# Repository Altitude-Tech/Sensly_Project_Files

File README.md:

# Sensly_Project_Files-
All files required for the production of the Sensly Air Quality Development Board

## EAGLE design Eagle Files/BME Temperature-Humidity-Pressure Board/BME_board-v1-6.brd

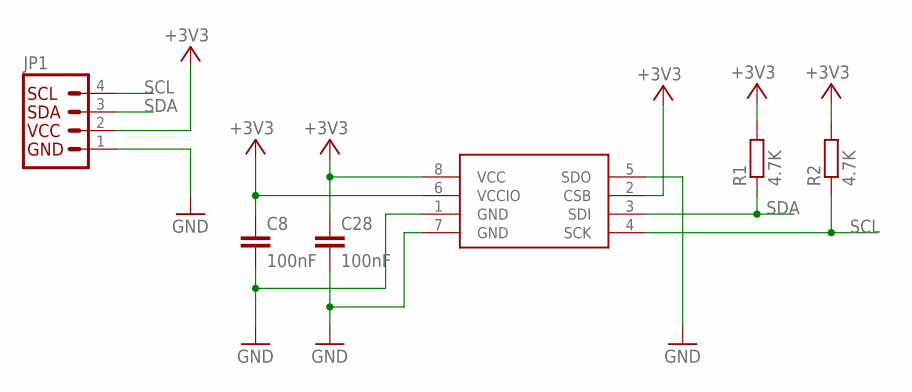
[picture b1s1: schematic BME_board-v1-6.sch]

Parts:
C8, C28: 100nF; C0603
IC2: BME280
JP1: I2C_STANDARD; 1X04
R1, R2: 4.7K; R0603

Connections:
+3V3: C8.1, C28.1, IC2.2 (CSB), IC2.6 (VCCIO), IC2.8 (VCC), JP1.2, R1.2, R2.2
GND: C8.2, C28.2, IC2.1 (GND), IC2.5 (SDO), IC2.7 (GND), JP1.1
SCL: IC2.4 (SCK), JP1.4, R2.1
SDA: IC2.3 (SDI), JP1.3, R1.1

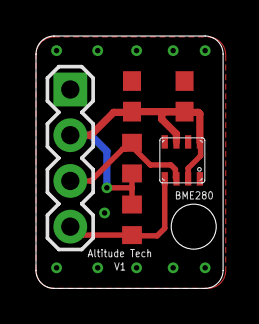
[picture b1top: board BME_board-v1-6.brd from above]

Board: 2 copper layers, 10.4 x 14.0 mm, 6 parts (0 on the bottom side), 4 nets.

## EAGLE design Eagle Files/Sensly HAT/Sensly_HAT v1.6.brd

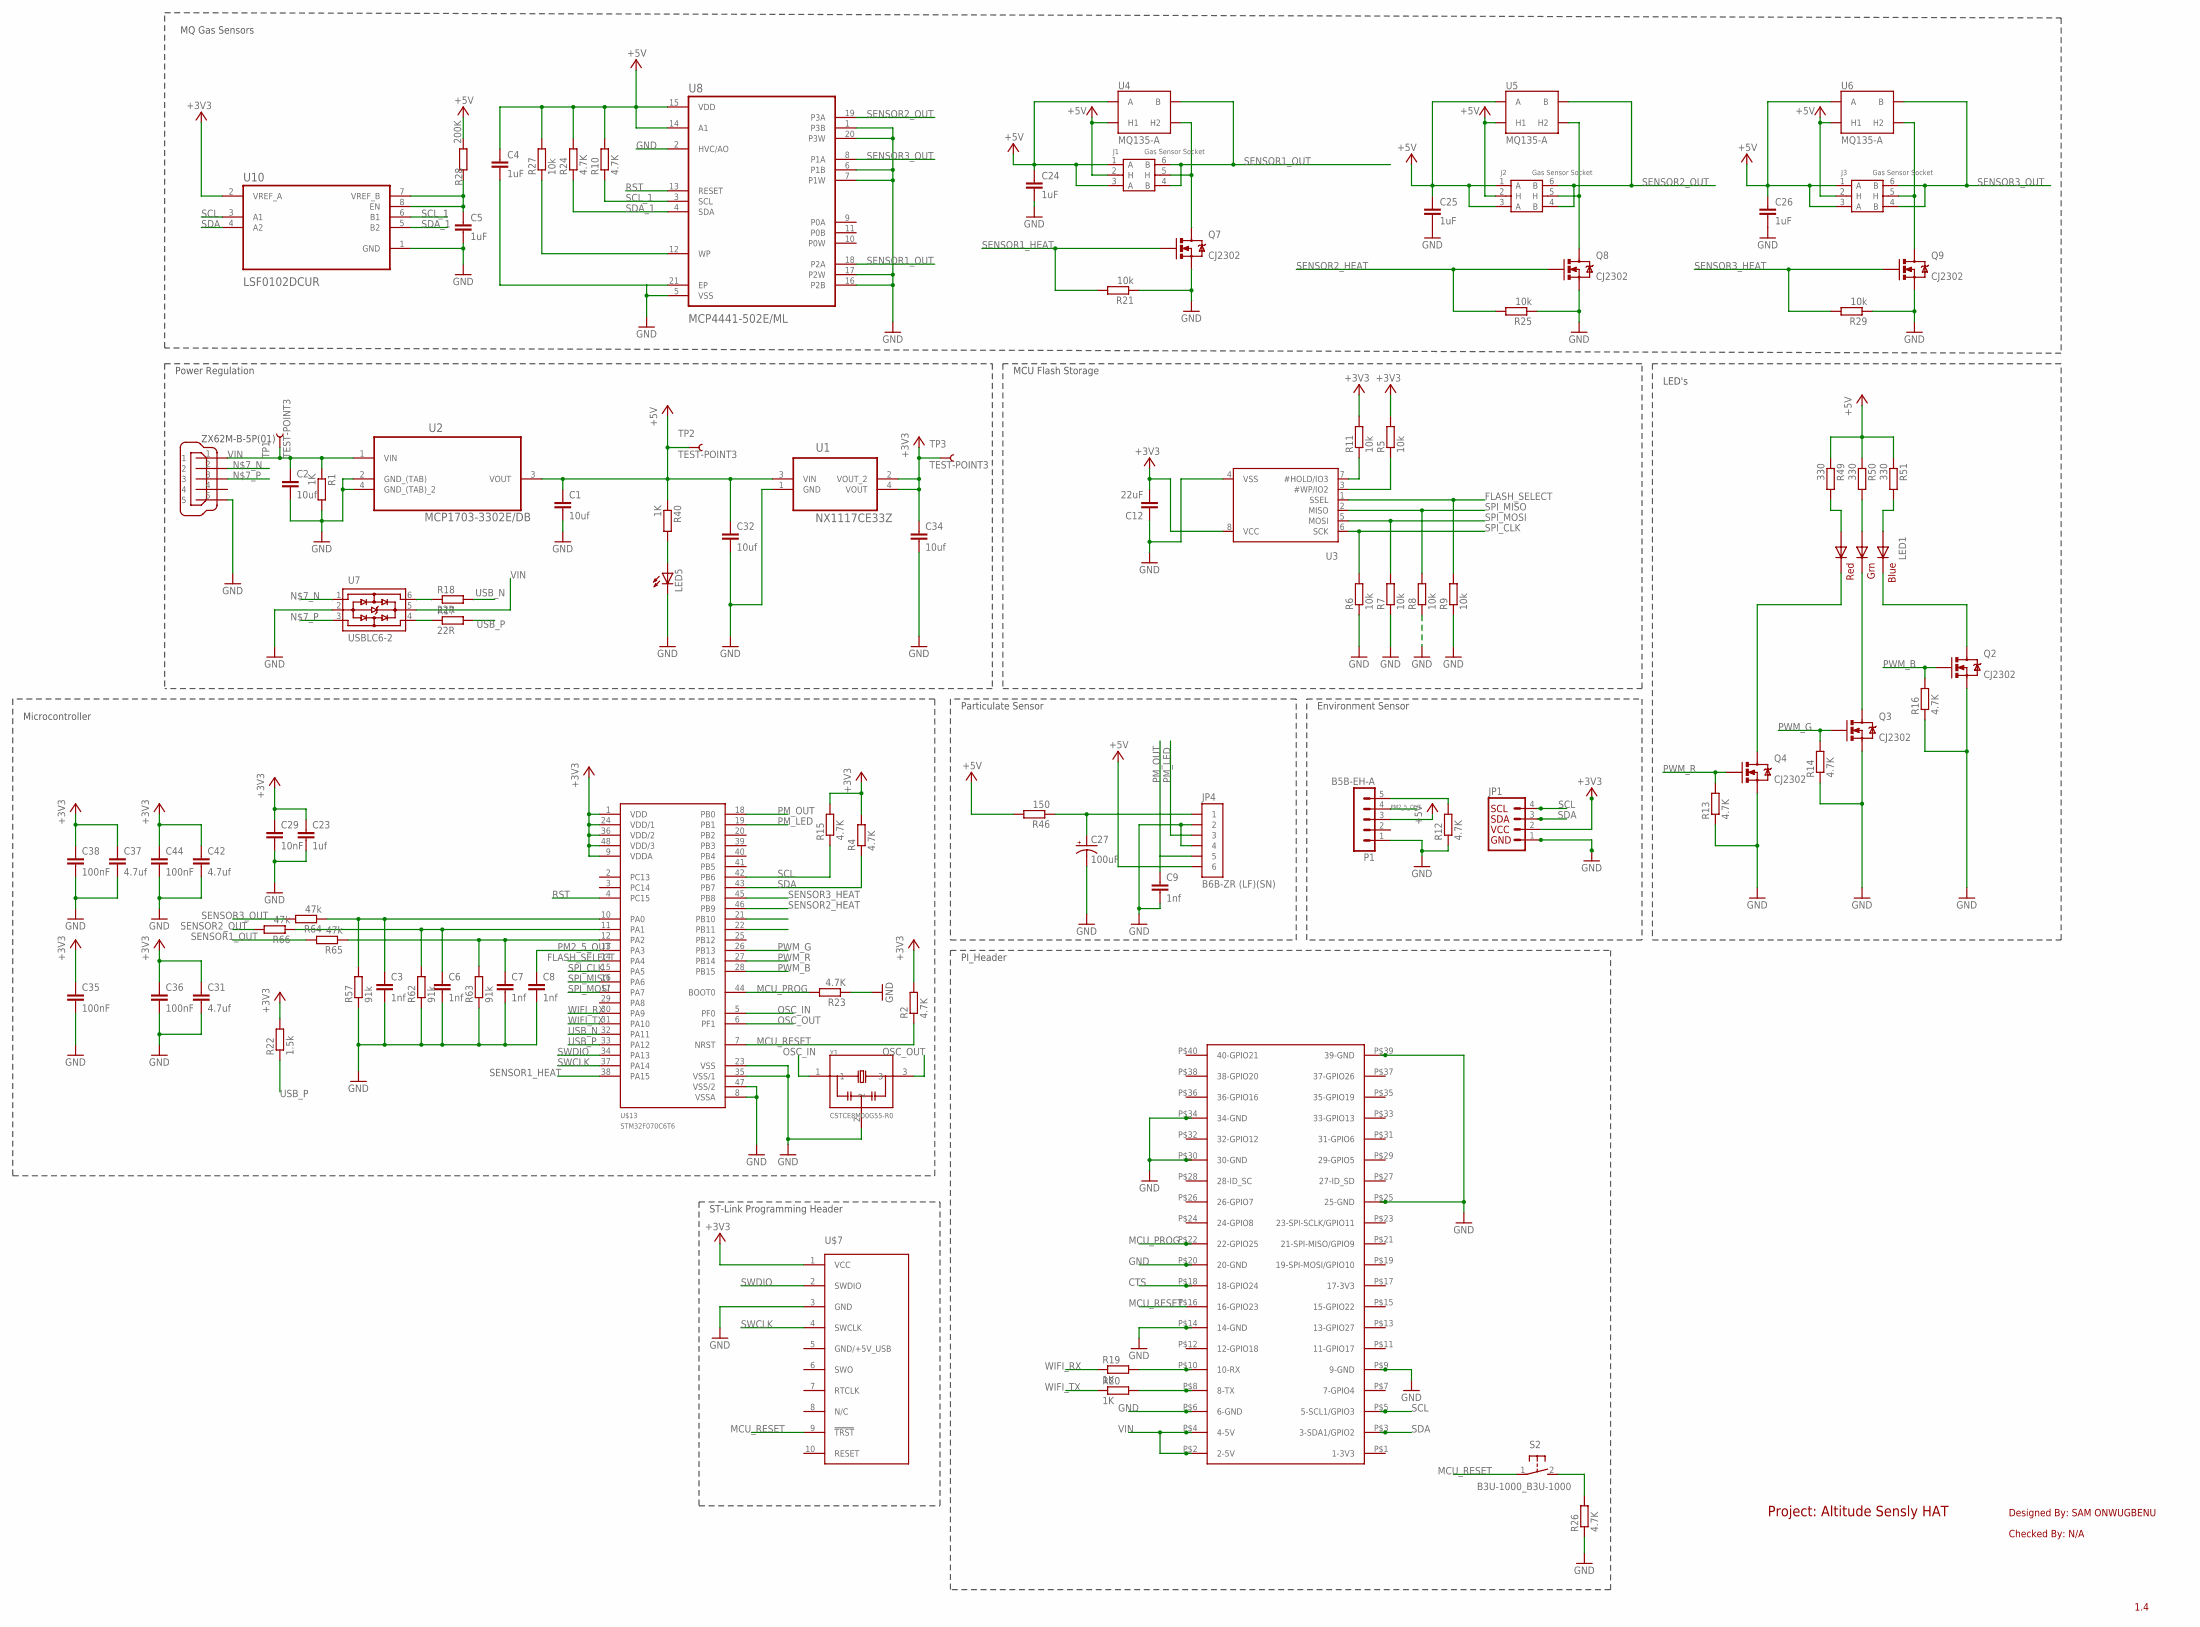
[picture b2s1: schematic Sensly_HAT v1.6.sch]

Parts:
C1, C2, C32, C34: 10uf; C0603
C3, C6, C7, C8, C9: 1nf; EAGLE-LTSPICE_C0402
C4, C5, C24, C25, C26: 1uF; 0603_N
C12: 22uF; C0603
C23: 1uf; C0603
C27: 100uF; EIA3216
C29: 10nF; C0603
C31, C37, C42: 4.7uf; C0603
C35, C36, C38, C44: 100nF; C0603
J1, J2, J3: Gas Sensor Socket; 6P-D17.6X9.8H
JP1: I2C_STANDARD; 1X04
JP4: B6B-ZR (LF)(SN); CONNECTOR_B6B-ZR
LED1: RGBLED5050
LED5: LEDCHIPLED_0603; CHIPLED_0603
P1: B5B-EH-A
Q2, Q3, Q4, Q7, Q8, Q9: CJ2302; SOT-23-3_N/SSOT-3_N
R1, R19, R20, R40: 1K; R0603
R2, R4, R10, R12, R13, R14, R15, R16, R23, R24, R26: 4.7K; R0603
R5, R6, R7, R8, R9, R11, R21, R25, R27, R29: 10k; R0603
R17, R18: 22R; R0603
R22: 1.5k; R0603
R28: 200K; R0603
R46: 150; R0603
R49, R50, R51: 330; R0603
R57, R62, R63: 91k; R0603
R64, R65, R66: 47k; R0603
S2: B3U-1000_B3U-1000; B3U-1000_B3U
TP1, TP2, TP3: TEST-POINT3; PAD.03X.03
U1: NX1117CE33Z; SOT230P700X180-4N
U2: MCP1703-3302E/DB; SOT230P700X180-4N
U3: SPIFLASH_SOIC8; SOIC8_150MIL
U4, U5, U6: MQ135-A
U7: USBLC6-2; USBLC6-2P6
U8: MCP4441-502E/ML; QFN50P400X400X100-21N
U10: LSF0102DCUR; SOP50P310X90-8N
U$2: RASPBERRY-PI+; RASPBERRY-PI-PLUS-CAM_NOTCH
U$7: TC2050-MCP-NL; TC2030-MCP-NL
U$9: ZX62M-B-5P(01); MICROUSB
U$13: STM32F070C6T6; QFP50P900X900X160-48N
Y1: CSTCE8M00G55-R0; OSC_CSTCE8M00G55-R0

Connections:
+3V3: C12.2, C23.1, C29.1, C31.1, C34.1, C35.1, C36.1, C37.1, C38.1, C42.1, C44.1, JP1.2, R2.2, R4.2, R5.2, R11.2, R15.2, R22.2, TP3.P$1, U1.2 (VOUT_2), U1.4 (VOUT), U3.8 (VCC), U10.2 (VREF_A), U$7.1 (VCC), U$13.1 (VDD), U$13.9 (VDDA), U$13.24 (VDD/1), U$13.36 (VDD/2), U$13.48 (VDD/3)
+5V: C1.1, C4.1, C24.1, C25.1, C26.1, C32.1, J1.1 (A), J1.2 (H), J1.3 (A), J2.1 (A), J2.2 (H), J2.3 (A), J3.1 (A), J3.2 (H), J3.3 (A), JP4.P$6 (6), P1.3, R10.2, R24.2, R27.2, R28.2, R40.1, R46.2, R49.1, R50.1, R51.1, TP2.P$1, U1.3 (VIN), U2.3 (VOUT), U4.1 (A), U4.2 (H1), U4.3 (A), U5.1 (A), U5.2 (H1), U5.3 (A), U6.1 (A), U6.2 (H1), U6.3 (A), U8.14 (A1), U8.15 (VDD)
CTS: U$2.P$18 (18-GPIO24)
FLASH_SELECT: R9.2, U3.1 (SSEL), U$13.14 (PA4)
GND: C1.2, C2.2, C3.2, C4.2, C5.2, C6.2, C7.2, C8.2, C9.2, C12.1, C23.2, C24.2, C25.2, C26.2, C27.C (-), C29.2, C31.2, C32.2, C34.2, C35.2, C36.2, C37.2, C38.2, C42.2, C44.2, JP1.1, JP4.P$2 (2), JP4.P$4 (4), LED5.C, P1.1, Q2.2 (S), Q3.2 (S), Q4.2 (S), Q7.2 (S), Q8.2 (S), Q9.2 (S), R1.2, R6.1, R7.1, R8.1, R9.1, R12.1, R13.1, R14.1, R16.1, R21.1, R23.1, R25.1, R26.1, R29.1, R57.1, R62.1, R63.1, U1.1 (GND), U2.2 (GND_(TAB)), U2.4 (GND_(TAB)_2), U3.4 (VSS), U7.2, U8.1 (P3B), U8.2 (HVC/AO), U8.5 (VSS), U8.6 (P1B), U8.7 (P1W), U8.16 (P2B), U8.17 (P2W), U8.20 (P3W), U8.21 (EP), U10.1 (GND), U$2.P$6 (6-GND), U$2.P$9 (9-GND), U$2.P$14 (14-GND), U$2.P$20 (20-GND), U$2.P$25 (25-GND), U$2.P$30 (30-GND), U$2.P$34 (34-GND), U$2.P$39 (39-GND), U$7.3 (GND), U$9.5, U$13.8 (VSSA), U$13.23 (VSS), U$13.35 (VSS/1), U$13.47 (VSS/2), Y1.2
MCU_PROG: R23.2, U$2.P$22 (22-GPIO25), U$13.44 (BOOT0)
MCU_RESET: R2.1, S2.1, U$2.P$16 (16-GPIO23), U$7.9 (!TRST), U$13.7 (NRST)
unnamed: LED1.5 (RED_C), Q4.3 (D)
unnamed: LED5.A, R40.2
unnamed: P1.5, R12.2
unnamed: R26.2, S2.2
unnamed: U7.1, U$9.2
unnamed: U7.3, U$9.3
unnamed: R19.2, U$2.P$10 (10-RX)
unnamed: R20.2, U$2.P$8 (8-TX)
unnamed: R27.1, U8.12 (WP)
unnamed: R5.1, U3.3 (#WP/IO2)
unnamed: C5.1, R28.1, U10.7 (VREF_B), U10.8 (EN)
unnamed: R18.1, U7.6
unnamed: R17.1, U7.4
unnamed: R11.1, U3.7 (#HOLD/IO3)
unnamed: LED1.4 (BLUE_C), Q2.3 (D)
unnamed: J1.5 (H), Q7.3 (D), U4.5 (H2)
unnamed: LED1.6 (GREEN_C), Q3.3 (D)
unnamed: J2.5 (H), Q8.3 (D), U5.5 (H2)
unnamed: J3.5 (H), Q9.3 (D), U6.5 (H2)
unnamed: C27.A (+), JP4.P$1 (1), R46.1
unnamed: LED1.1 (GREEN_A), R50.2
unnamed: LED1.3 (BLUE_A), R51.2
unnamed: LED1.2 (RED_A), R49.2
OSC_IN: U$13.5 (PF0), Y1.1
OSC_OUT: U$13.6 (PF1), Y1.3
PM2_5_OUT: C8.1, P1.4, U$13.13 (PA3)
PM_LED: JP4.P$3 (3), U$13.19 (PB1)
PM_OUT: C9.1, JP4.P$5 (5), U$13.18 (PB0)
PWM_B: Q2.1 (G), R16.2, U$13.28 (PB15)
PWM_G: Q3.1 (G), R14.2, U$13.26 (PB13)
PWM_R: Q4.1 (G), R13.2, U$13.27 (PB14)
RST: U8.13 (RESET), U$13.4 (PC15)
SCL: JP1.4, R15.1, U10.3 (A1), U$2.P$5 (5-SCL1/GPIO3), U$13.42 (PB6)
SCL_1: R10.1, U8.3 (SCL), U10.6 (B1)
SDA: JP1.3, R4.1, U10.4 (A2), U$2.P$3 (3-SDA1/GPIO2), U$13.43 (PB7)
SDA_1: R24.1, U8.4 (SDA), U10.5 (B2)
SENSOR1_HEAT: Q7.1 (G), R21.2, U$13.38 (PA15)
SENSOR1_OUT: J1.4 (B), J1.6 (B), R65.2, U4.4 (B), U4.6 (B), U8.18 (P2A)
SENSOR1_OUT1: C7.1, R63.2, R65.1, U$13.12 (PA2)
SENSOR2_HEAT: Q8.1 (G), R25.2, U$13.46 (PB9)
SENSOR2_OUT: J2.4 (B), J2.6 (B), R66.2, U5.4 (B), U5.6 (B), U8.19 (P3A)
SENSOR2_OUT1: C6.1, R62.2, R66.1, U$13.11 (PA1)
SENSOR3_HEAT: Q9.1 (G), R29.2, U$13.45 (PB8)
SENSOR3_OUT: J3.4 (B), J3.6 (B), R64.2, U6.4 (B), U6.6 (B), U8.8 (P1A)
SENSOR3_OUT1: C3.1, R57.2, R64.1, U$13.10 (PA0)
SPI_CLK: R6.2, U3.6 (SCK), U$13.15 (PA5)
SPI_MISO: R8.2, U3.2 (MISO), U$13.16 (PA6)
SPI_MOSI: R7.2, U3.5 (MOSI), U$13.17 (PA7)
SWCLK: U$7.4 (SWCLK), U$13.37 (PA14)
SWDIO: U$7.2 (SWDIO), U$13.34 (PA13)
USB_N: R18.2, U$13.32 (PA11)
USB_P: R17.2, R22.1, U$13.33 (PA12)
VIN: C2.1, R1.1, TP1.P$1, U2.1 (VIN), U7.5, U$2.P$2 (2-5V), U$2.P$4 (4-5V), U$9.1
WIFI_RX: R19.1, U$13.30 (PA9)
WIFI_TX: R20.1, U$13.31 (PA10)

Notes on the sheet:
Power Regulation
MQ Gas Sensors
Particulate Sensor
Environment Sensor
1.4
Designed By: SAM ONWUGBENU
Checked By: N/A
Project: Altitude Sensly HAT
MCU Flash Storage
LED's
PI_Header
ST-Link Programming Header
Microcontroller

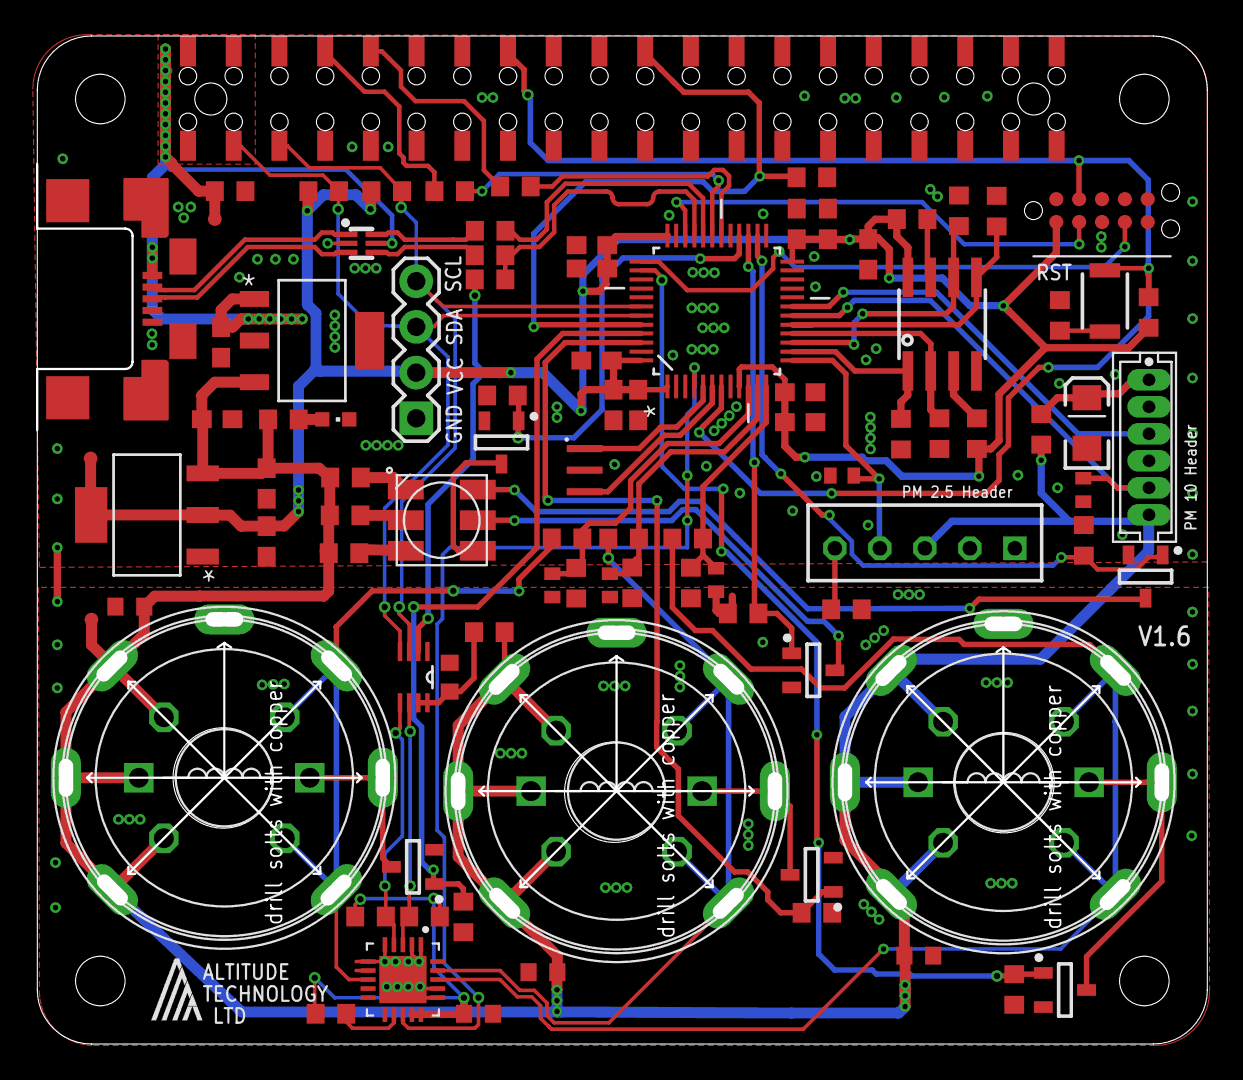
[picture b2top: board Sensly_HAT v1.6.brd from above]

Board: 2 copper layers, 65.0 x 56.0 mm, 96 parts (0 on the bottom side), 61 nets.

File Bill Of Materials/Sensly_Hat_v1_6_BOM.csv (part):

Qty,Line Item,Manufacturer,MPN,Octopart URL,Schematic Reference,Internal Part Number,Description,Total Qty (@ Batch Size: 10),SKU,SKU,SKU,SKU,Packaging,Packaging,Packaging,Packaging,Unit Price (@ Batch Size: 10),Unit Price (@ Batch Size: 10),Unit Price (@ Batch Size: 10),Unit Price (@ Batch Size: 10),In Stock,In Stock,In Stock,In Stock,MOQ,MOQ,MOQ,MOQ,URL,URL,URL,URL,Distributor [Lowest Price (Overall)],SKU [Lowest Price (Overall)],Packaging [Lowest Price (Overall)],Unit Price (@ Batch Size: 10) [Lowest Price (Overall)],Line Total [Lowest Price (Overall)],Batch Total [Lowest Price (Overall)],In Stock [Lowest Price (Overall)],MOQ [Lowest Price (Overall)],URL [Lowest Price (Overall)],Notes
,,,,,,,,,Digi-Key,Farnell,Future Electronics,Mouser,Digi-Key,Farnell,Future Electronics,Mouser,Digi-Key,Farnell,Future Electronics,Mouser,Digi-Key,Farnell,Future Electronics,Mouser,Digi-Key,Farnell,Future Electronics,Mouser,Digi-Key,Farnell,Future Electronics,Mouser,,,,,,,,,,
5,MC0402B102J250CT,Multicomp,MC0402B102J250CT,https://octopart.com/mc0402b102j250ct-multicomp-75361321,"C3, C6, C7, C8, C9",,1nF 0402 CAPACITOR,50,,2627336,,,,,,,,0.0261,,,,29766,,,,10,,,,https://octopart.com/click/track?ak=39ac400e&sig=0fc9e01&sid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,,,element14 APAC,2627336,,0.011457687748570549,0.05728843874285274,0.5728843874285274,24430,10,https://octopart.com/click/track?ak=39ac400e&sig=0845a5a&sid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,
1,C0603C103K3HACAUTO,KEMET,C0603C103K3HACAUTO,https://octopart.com/c0603c103k3hacauto-kemet-22427073,C5,,10nF 0603 CAPACITOR,10,399-12971-1-ND,2773118,,80-C0603C103K3HAUTO,Cut Tape,,,,0.105755614,0.164,,0.105755614,30882,7409,,27990,1,10,,1,https://octopart.com/click/track?ak=39ac400e&sig=0a98e63&sid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,https://octopart.com/click/track?ak=39ac400e&sig=0ab396f&sid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,,https://octopart.com/click/track?ak=39ac400e&sig=0935c6b&sid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,Newark,06AH2423,Cut Tape,0.044985597,0.044985597,0.44985597,4000,1,https://octopart.com/click/track?ak=39ac400e&sig=02e2569&sid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,
2,MCB0603R104KCT,Multicomp,MCB0603R104KCT,https://octopart.com/mcb0603r104kct-multicomp-46923379,"C35, C36, C38, C44",,0.1uF 0603 CAPACITOR,20,,9406140,,,,,,,,0.0445,,,,54128,,,,10,,,,https://octopart.com/click/track?ak=39ac400e&sig=0d37946&sid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,,,element14 APAC,9406140,,0.022915375497141097,0.045830750994282195,0.45830750994282193,61638,10,https://octopart.com/click/track?ak=39ac400e&sig=08e6c11&sid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,
6,0603F105Z100CT,Walsin Technologies,0603F105Z100CT,https://octopart.com/0603f105z100ct-walsin+technologies-42888023,"C4, C5, C23,  C24, C25, C26",,1uF 0603 Capacitor,60,,2524858,0603F105Z100CT-CUTT,791-0603F105Z100CT,,,Cut Tape,,,0.0993,0.042775778199999996,0.036304166,,17550,3450,0,,10,1,1,,https://octopart.com/click/track?ak=39ac400e&sig=0942e30&sid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,https://octopart.com/click/track?ak=39ac400e&sig=0a2de7a&sid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,https://octopart.com/click/track?c=1&ak=39ac400e&sig=004a669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,element14 APAC,2524858,,0.016613647235427298,0.09968188341256379,0.9968188341256379,17081,10,https://octopart.com/click/track?ak=39ac400e&sig=0b813df&sid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,
3,0603F475Z6R3CT,Walsin Technologies,0603F475Z6R3CT,https://octopart.com/0603f475z6r3ct-walsin+technologies-23758823,"C31, C37,C42",,4.7 uF 0603 CAPACITOR,30,,2524874,,,,,,,,0.166,,,,4430,,,,10,,,,https://octopart.com/click/track?ak=39ac400e&sig=06f7b8e&sid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,,,element14 APAC,2524874,,0.03208152569599754,0.09624457708799261,0.9624457708799261,7339,10,https://octopart.com/click/track?ak=39ac400e&sig=00ca086&sid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,
4,GRM188R60G106ME47D,Murata,GRM188R60G106ME47D,https://octopart.com/grm188r60g106me47d-murata-196917,"C1, C2, C32, C34",,10uF 0603 CAPACITOR,40,490-3298-1-ND,2688517,,81-GRM188R60G106ME47,Cut Tape,,,,0.204408239,0.266,,0.22492798499999997,1244629,0,,70682,1,10,,1,https://octopart.com/click/track?ak=39ac400e&sig=04d283f&sid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,https://octopart.com/click/track?c=1&ak=39ac400e&sig=02c4790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,,https://octopart.com/click/track?ak=39ac400e&sig=0ad7f33&sid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,Quest,GRM188R60G106ME47D,,0.047353259999999994,0.18941303999999998,1.8941303999999999,5890,1,https://octopart.com/click/track?ak=39ac400e&sig=0819e9b&sid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,
1,C1608X5R0J226M080AC,TDK,C1608X5R0J226M080AC,https://octopart.com/c1608x5r0j226m080ac-tdk-26013464,C12,,22uF 0603 CAPACITOR,10,445-8028-1-ND,2525088,C1608X5R0J226M080AC-CUTT,810-C1608X5R0J226M,Cut Tape,,Cut Tape,,0.261232151,0.313,0.101020288,0.261232151,454406,0,520,179902,1,10,1,1,https://octopart.com/click/track?ak=39ac400e&sig=0cc20cd&sid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,https://octopart.com/click/track?c=1&ak=39ac400e&sig=0f25aee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,https://octopart.com/click/track?ak=39ac400e&sig=0d342f3&sid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,https://octopart.com/click/track?ak=39ac400e&sig=05a7d84&sid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,Future Electronics,C1608X5R0J226M080AC-CUTT,Cut Tape,0.101020288,0.101020288,1.01020288,520,1,https://octopart.com/click/track?ak=39ac400e&sig=0d342f3&sid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,
1,TAJA107K002RNJ,AVX,TAJA107K002RNJ,https://octopart.com/taja107k002rnj-avx-19796623,C27,,100uF 1206 Tantalum Capacitor,10,TAJA107K002RNJ-ND,1658139,,581-TAJA107K002RNJ,Tape & Reel,,,,,0.566,,0.46642961099999997,0,1593,,1730,2000,5,,1,https://octopart.com/click/track?c=1&ak=39ac400e&sig=0bd9ac7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,https://octopart.com/click/track?ak=39ac400e&sig=028aef2&sid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,,https://octopart.com/click/track?ak=39ac400e&sig=0966c63&sid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,Mouser,581-TAJA107K002RNJ,,0.46642961099999997,0.46642961099999997,4.6642961099999996,1730,1,https://octopart.com/click/track?ak=39ac400e&sig=0966c63&sid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,
2,ERJ-3EKF22R0V,Panasonic,ERJ-3EKF22R0V,https://octopart.com/erj-3ekf22r0v-panasonic-9231677,"R17, R18",,"22R RESISTOR, European symbol",20,P22.0HCT-ND,2302996,ERJ-3EKF22R0V-REEL,667-ERJ-3EKF22R0V,Cut Tape,,Tape & Reel,,0.051299365,0.0378,,0.029990397999999998,1382229,60158,30000,396408,1,10,5000,1,https://octopart.com/click/track?ak=39ac400e&sig=0466c3b&sid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,https://octopart.com/click/track?ak=39ac400e&sig=0d001b6&sid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,https://octopart.com/click/track?ak=39ac400e&sig=005237e&sid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,https://octopart.com/click/track?ak=39ac400e&sig=08f095d&sid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,Avnet,ERJ-3EKF22R0V,,0.00555611584,0.01111223168,0.1111223168,122,1,https://octopart.com/click/track?ak=39ac400e&sig=0aebd43&sid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,
1,ERJ-3EKF1500V,Panasonic,ERJ-3EKF1500V,https://octopart.com/erj-3ekf1500v-panasonic-55421487,R46,,150R 0603 RESISTOR,10,P150HCT-ND,2303076,ERJ-3EKF1500V-CUTT,667-ERJ-3EKF1500V,Cut Tape,,Cut Tape,,0.051299365,0.0374,0.0065505343,0.029990397999999998,857632,27483,2300,252754,1,10,1,1,https://octopart.com/click/track?ak=39ac400e&sig=07b7d2b&sid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,https://octopart.com/click/track?ak=39ac400e&sig=03ddd24&sid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,https://octopart.com/click/track?ak=39ac400e&sig=0ba0667&sid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,https://octopart.com/click/track?ak=39ac400e&sig=0202b7b&sid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,Avnet,ERJ-3EKF1500V,,0.00555611584,0.00555611584,0.0555611584,474,1,https://octopart.com/click/track?ak=39ac400e&sig=0767aa2&sid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,
3,ERJ-3EKF3300V,Panasonic,ERJ-3EKF3300V,https://octopart.com/erj-3ekf3300v-panasonic-9251137,"R49, R50, R51",,330R 0603 RESISTOR,30,P330HCT-ND,2303104,ERJ-3EKF3300V-CUTT,667-ERJ-3EKF3300V,Cut Tape,,Cut Tape,,0.051299365,0.0378,0.0080500542,0.029990397999999998,2654457,15617,3281,1005936,1,10,1,1,https://octopart.com/click/track?ak=39ac400e&sig=0353c2a&sid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,https://octopart.com/click/track?ak=39ac400e&sig=0643127&sid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,https://octopart.com/click/track?ak=39ac400e&sig=03073c8&sid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,https://octopart.com/click/track?ak=39ac400e&sig=06e992b&sid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,Smith & Associates,PANASO.ERJ3EKF3300V,,0.0019730525,0.0059191575,0.059191574999999996,25000,1,https://octopart.com/click/track?ak=39ac400e&sig=0e2d2f3&sid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,
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
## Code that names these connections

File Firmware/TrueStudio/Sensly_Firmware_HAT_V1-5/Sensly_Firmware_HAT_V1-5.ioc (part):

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Mcu.Name=STM32F103C(8-B)Tx
Mcu.Package=LQFP48
Mcu.UserName=STM32F103C8Tx
PA0-WKUP.GPIOParameters=GPIO_Label
PA0-WKUP.GPIO_Label=Sensor_Data_1
PA0-WKUP.Signal=ADCx_IN0
PA1.GPIOParameters=GPIO_Label
PA1.GPIO_Label=Sensor_Data_2
PA1.Signal=ADCx_IN1
PA13.Mode=Serial_Wire
PA13.Signal=SYS_JTMS-SWDIO
PA14.Mode=Serial_Wire
PA14.Signal=SYS_JTCK-SWCLK
PA15.Signal=GPIO_Output
PA2.GPIOParameters=GPIO_Label
PA2.GPIO_Label=Sensor_Data_3
PA2.Signal=ADCx_IN2
PA3.GPIOParameters=GPIO_Label
PA3.GPIO_Label=PM2_5_Out
PA3.Signal=ADCx_IN3
PA4.GPIOParameters=GPIO_Label
PA4.GPIO_Label=Flash_Select
PA4.Signal=GPIO_Output
PA5.Mode=Full_Duplex_Master
PA5.Signal=SPI1_SCK
PA6.Mode=Full_Duplex_Master
PA6.Signal=SPI1_MISO
PA7.Mode=Full_Duplex_Master
PA7.Signal=SPI1_MOSI
PB0.GPIOParameters=GPIO_Label
PB0.GPIO_Label=PM_Data
PB0.Signal=ADCx_IN8
PB1.GPIOParameters=GPIO_Label
PB1.GPIO_Label=PM_LED
PB1.Signal=GPIO_Output
PB13.GPIOParameters=GPIO_Label
PB13.GPIO_Label=PWM_B
PB13.Mode=PWM Generation1 CH1N
PB13.Signal=TIM1_CH1N
PB14.GPIOParameters=GPIO_Label
PB14.GPIO_Label=PWM_R
PB14.Mode=PWM Generation2 CH2N
PB14.Signal=TIM1_CH2N
PB15.GPIOParameters=GPIO_Label
PB15.GPIO_Label=PWM_G
PB15.Mode=PWM Generation3 CH3N
PB15.Signal=TIM1_CH3N
PB6.Mode=I2C
PB6.Signal=I2C1_SCL
PB7.Mode=I2C
PB7.Signal=I2C1_SDA
PB8.Signal=GPIO_Output
PB9.GPIOParameters=GPIO_Label
PB9.GPIO_Label=Sensor_2_Heat
PB9.Signal=S_TIM4_CH4
PD0-OSC_IN.Mode=HSE-External-Oscillator
PD0-OSC_IN.Signal=RCC_OSC_IN
PD1-OSC_OUT.Mode=HSE-External-Oscillator
PD1-OSC_OUT.Signal=RCC_OSC_OUT
RCC.SYSCLKFreq_VALUE=48000000
RCC.SYSCLKSource=RCC_SYSCLKSOURCE_PLLCLK
board=Sensly_Firmware_V4

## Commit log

2019-06-04 Added True Studio Files

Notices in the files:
parts and their libraries:
SparkFun-Connectors: Licensing: Creative Commons ShareAlike 4.0 International - https://creativecommons.org/licenses/by-sa/4.0
microbuilder: This work is placed in the public domain, and may be freely used for commercial and non-commercial work with the following conditions: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
